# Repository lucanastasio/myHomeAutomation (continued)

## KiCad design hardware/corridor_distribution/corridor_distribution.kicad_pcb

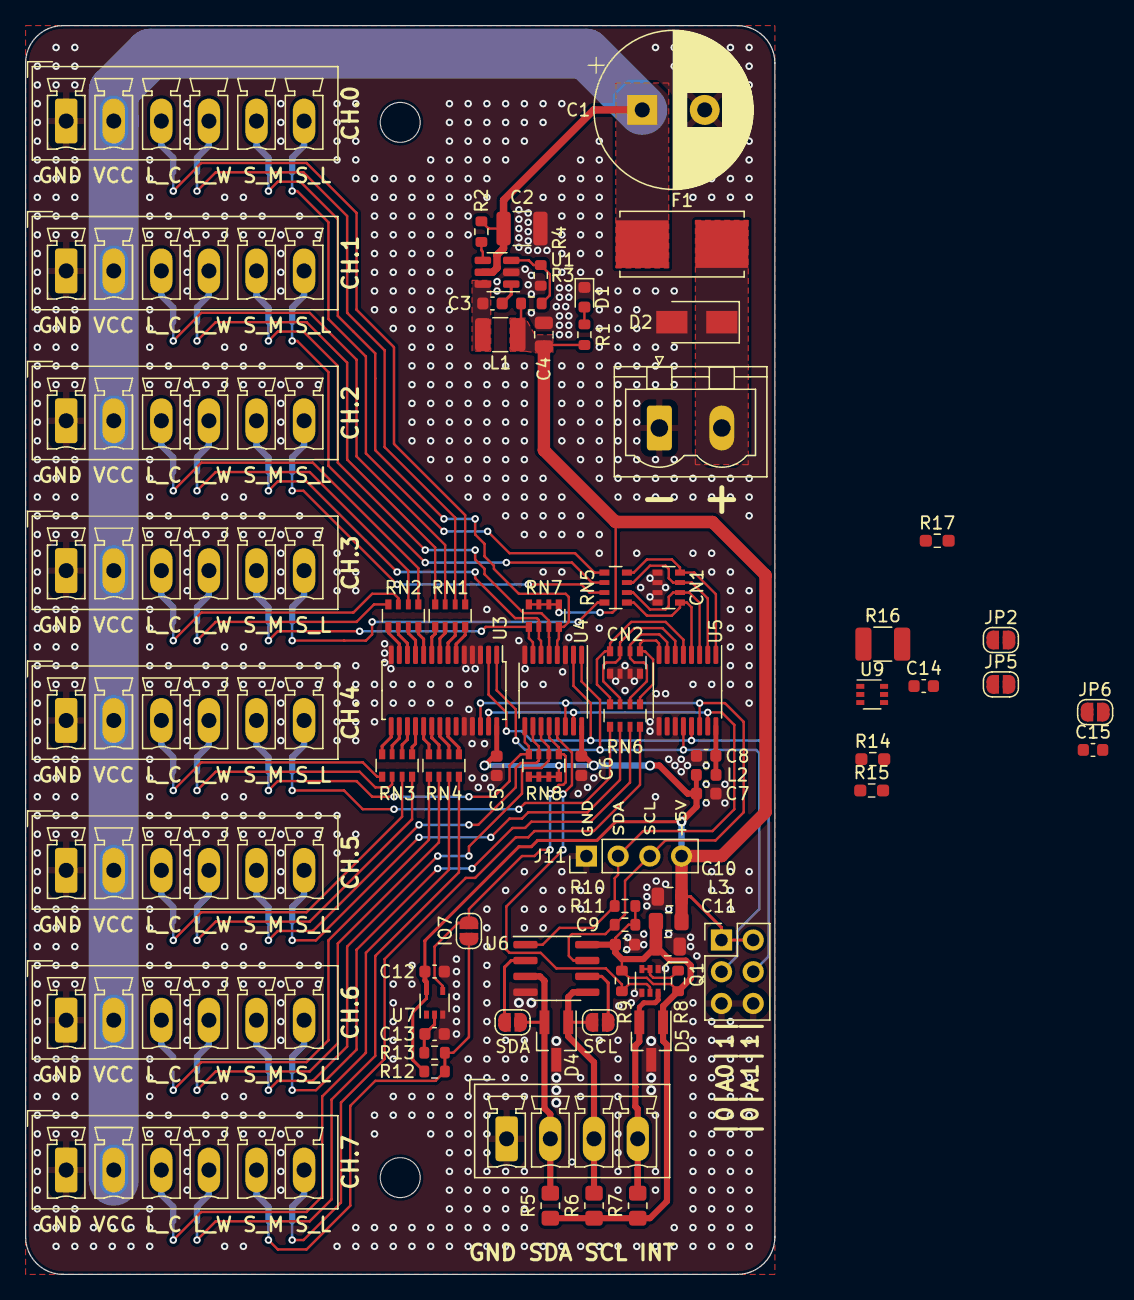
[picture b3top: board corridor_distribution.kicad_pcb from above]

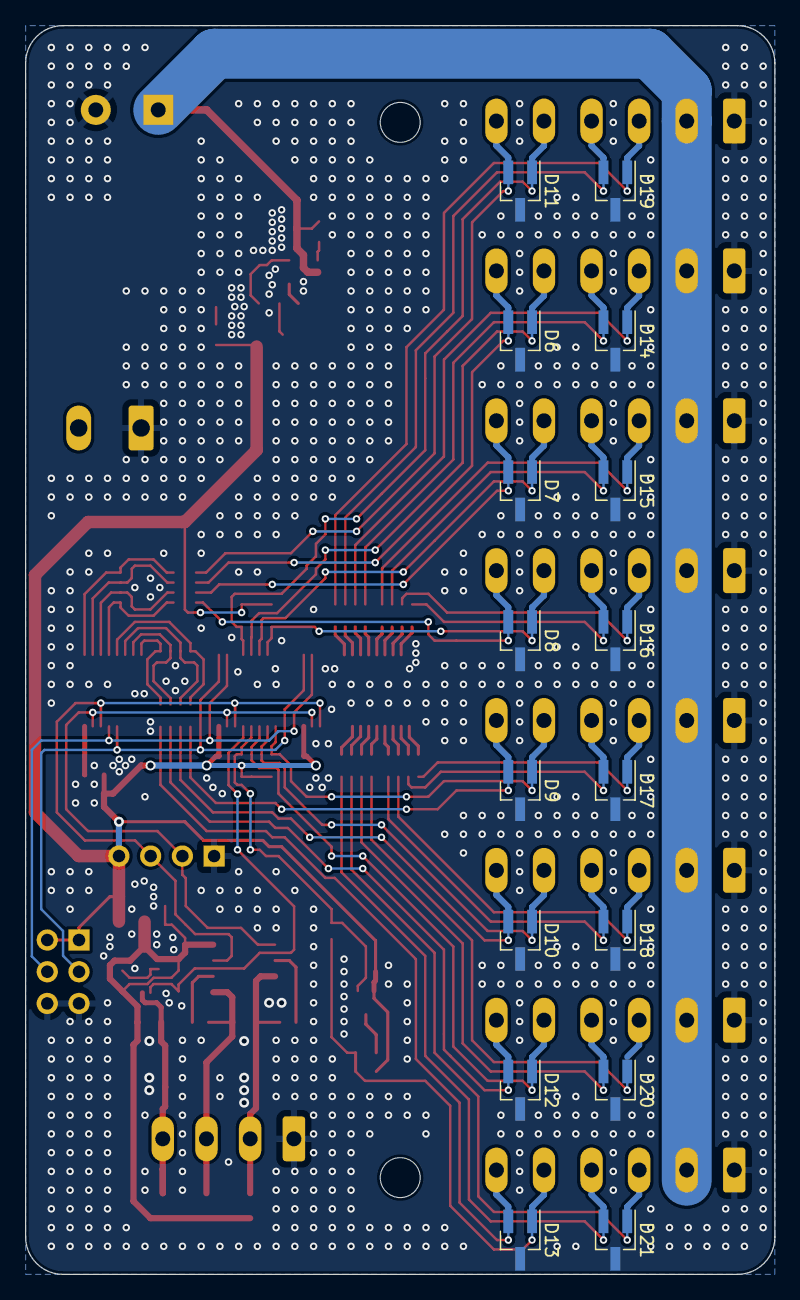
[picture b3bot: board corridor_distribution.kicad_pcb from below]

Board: 2 copper layers, 60.0 x 100.0 mm, 94 parts (16 on the bottom side), 86 nets.

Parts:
C1: 1000uF 50V D12.5xL25mm; CP_Radial_D12.5mm_P5.00mm
C2: 10u 50V; C_1210_3225Metric
C3, C5, C6, C7, C8, C9, C12, C13, C14, C15: 100n 50V; C_0603_1608Metric
C4, C10, C11: 22u 10V; C_0805_2012Metric
CN1, CN2: 100n 50V; R_Array_Convex_4x0603
D1: green LED; LED_0603_1608Metric
D2: SMAJ36A; D_SMA
D4, D5, D6, D7, D8, D9, D10, D11, D12, D13, D14, D15, D16, D17, D18, D19, D20, D21: SM05; SOT-23_Handsoldering
F1: 01550900M; Fuseholder_Littelfuse_Nano2_154x
H1, H2: MountingHole; MountingHole_3.2mm_M3
J1, J2, J3, J4, J5, J6, J7, J8: Screw_Terminal_01x06; PhoenixContact_MCV_1,5_6-G-3.81_1x06_P3.81mm_Vertical
J9: Screw_Terminal_01x02; PhoenixContact_MSTBVA_2,5_2-G_1x02_P5.00mm_Vertical
J10: Screw_Terminal_01x04; PhoenixContact_MCV_1,5_4-G-3.5_1x04_P3.50mm_Vertical
J11: Conn_01x04; PinHeader_1x04_P2.54mm_Vertical
J12: Conn_02x03_Odd_Even; PinHeader_2x03_P2.54mm_Vertical
JP1: IO7; SolderJumper-2_P1.3mm_Open_RoundedPad1.0x1.5mm
JP2, JP5, JP6: SolderJumper_2_Open; SolderJumper-2_P1.3mm_Open_RoundedPad1.0x1.5mm
JP3: SCL; SolderJumper-2_P1.3mm_Open_RoundedPad1.0x1.5mm
JP4: SDA; SolderJumper-2_P1.3mm_Open_RoundedPad1.0x1.5mm
L1: CBC3225T220KR; L_1210_3225Metric
L2: BLM18BD252SN1D; L_0603_1608Metric
L3: MMZ2012R102AT000; L_0805_2012Metric_Pad1.15x1.40mm_HandSolder
Q1: DMN2004DWK; SOT-363_SC-70-6
R1: 2.2k; R_0603_1608Metric
R2: 1M; R_0603_1608Metric
R3: 105k 0.5%; R_0603_1608Metric
R4: 20k 0.5%; R_0603_1608Metric
R5, R6, R7: 200; R_0805_2012Metric_Pad1.20x1.40mm_HandSolder
R8: 47k; R_0603_1608Metric
R9: 10k; R_0603_1608Metric
R10, R11, R12: 4.7k; R_0603_1608Metric
R13: 100k; R_0603_1608Metric
R14, R15: 330; R_0603_1608Metric_Pad0.98x0.95mm_HandSolder
R16: R; R_1210_3225Metric_Pad1.30x2.65mm_HandSolder
R17: R; R_0603_1608Metric_Pad0.98x0.95mm_HandSolder
RN1, RN2, RN3, RN4: 100; R_Array_Convex_4x0603
RN5, RN6: 68k; R_Array_Convex_4x0603
RN7, RN8: 4.7k; R_Array_Convex_4x0603
U1: TD1469; SOT-23-6
U3: PCA9685PW; TSSOP-28_4.4x9.7mm_P0.65mm
U4: TCA9554APW; TSSOP-16_4.4x5mm_P0.65mm
U5: ADS7830; TSSOP-16_4.4x5mm_P0.65mm
U6: P82B96; SOIC-8_3.9x4.9mm_P1.27mm
U7: 74LVC1G17; SOT-353_SC-70-5
U9: INA190; SOT-363_SC-70-6

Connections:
+5V: C4.2, C5.1, C6.1, C7.1, C10.1, C12.1, C14.1, J11.4, J12.1, J12.2, L1.2, L2.1, L3.1, R1.1, R3.1, R12.2, RN7.1 (R1.1), RN7.2 (R2.1), RN7.3 (R3.1), RN7.4 (R4.1), RN8.1 (R1.1), RN8.2 (R2.1), RN8.3 (R3.1), RN8.4 (R4.1), U3.28 (VDD), U4.16 (VDD), U7.5 (VCC), U9.3 (V+)
+5VA: C8.1, JP6.1 (A), L2.2, U5.16 (VDD)
+5VD: C9.1, C11.1, D5.1 (A1), L3.2, R5.1, R6.1, R7.1, R8.1, R9.1, R10.1, R11.1, U6.8 (VCC)
+36V: C1.1, C2.2, J1.2, J2.2, J3.2, J4.2, J5.2, J6.2, J7.2, J8.2, R2.2, R16.2, U1.5 (VIN), U9.5 (-)
/A0: J12.3, U3.1 (A0), U4.1 (A0), U5.12 (A0)
/A1: J12.4, U3.2 (A1), U4.2 (A1), U5.13 (A1)
/ADC/AD0: D11.2 (A2), J6.6, RN5.5 (R4.2)
/ADC/AD1: D6.2 (A2), J1.6, RN5.6 (R3.2)
/ADC/AD2: D7.2 (A2), J2.6, RN5.7 (R2.2)
/ADC/AD3: D8.2 (A2), J3.6, RN5.8 (R1.2)
/ADC/AD4: D9.2 (A2), J4.6, RN6.5 (R4.2)
/ADC/AD5: D10.2 (A2), J5.6, RN6.6 (R3.2)
/ADC/AD6: D12.2 (A2), J7.6, RN6.7 (R2.2)
/ADC/AD7: D13.2 (A2), J8.6, RN6.8 (R1.2)
/ADC/REF: C15.1, JP6.2 (B), U5.10 (REFin/REFout)
/ADC/_AD0: CN1.4 (R4.1), RN5.4 (R4.1), U5.1 (CH0)
/ADC/_AD1: CN1.3 (R3.1), RN5.3 (R3.1), U5.2 (CH1)
/ADC/_AD2: CN1.2 (R2.1), RN5.2 (R2.1), U5.3 (CH2)
/ADC/_AD3: CN1.1 (R1.1), RN5.1 (R1.1), U5.4 (CH3)
/ADC/_AD4: CN2.4 (R4.1), RN6.4 (R4.1), U5.5 (CH4)
/ADC/_AD5: CN2.3 (R3.1), RN6.3 (R3.1), U5.6 (CH5)
/ADC/_AD6: CN2.2 (R2.1), RN6.2 (R2.1), U5.7 (CH6)
/ADC/_AD7: CN2.1 (R1.1), R17.2, RN6.1 (R1.1), U5.8 (CH7)
/IO/IO0: D11.1 (A1), J6.5, RN7.8 (R1.2), U4.4 (P0)
/IO/IO1: D6.1 (A1), J1.5, RN7.7 (R2.2), U4.5 (P1)
/IO/IO2: D7.1 (A1), J2.5, RN7.6 (R3.2), U4.6 (P2)
/IO/IO3: D8.1 (A1), J3.5, RN7.5 (R4.2), U4.7 (P3)
/IO/IO4: D9.1 (A1), J4.5, RN8.8 (R1.2), U4.9 (P4)
/IO/IO5: D10.1 (A1), J5.5, RN8.7 (R2.2), U4.10 (P5)
/IO/IO6: D12.1 (A1), J7.5, RN8.6 (R3.2), U4.11 (P6)
/IO/IO7: D13.1 (A1), J8.5, JP1.2 (B), R12.1, R13.1
/IO/IO7F: C13.1, R13.2, U7.2
/IO/IO7S: JP1.1 (A), RN8.5 (R4.2), U4.12 (P7), U7.4
/SCL: J11.3, R11.2, U3.26 (SCL), U4.14 (SCL), U5.14 (SCL), U6.7 (SCL)
/SDA: J11.2, R10.2, U3.27 (SDA), U4.15 (SDA), U5.15 (SDA), U6.1 (SDA)
/bus_in/INT: D5.2 (A2), J10.4, Q1.6 (D), R7.2
/bus_in/SCL_{R}: JP3.1 (A), U6.6 (RXD-SCL)
/bus_in/SCL_{T}: D4.1 (A1), J10.3, JP3.2 (B), R6.2, U6.5 (TXD-SCL)
/bus_in/SDA_{R}: JP4.1 (A), U6.2 (RXD-SDA)
/bus_in/SDA_{T}: D4.2 (A2), J10.2, JP4.2 (B), R5.2, U6.3 (TXD-SDA)
/nodes/PW0: D19.1 (A1), J6.3, RN1.5 (R4.2)
/nodes/PW1: D19.2 (A2), J6.4, RN1.6 (R3.2)
/nodes/PW2: D14.1 (A1), J1.3, RN1.7 (R2.2)
/nodes/PW3: D14.2 (A2), J1.4, RN1.8 (R1.2)
/nodes/PW4: D15.1 (A1), J2.3, RN2.5 (R4.2)
/nodes/PW5: D15.2 (A2), J2.4, RN2.6 (R3.2)
/nodes/PW6: D16.1 (A1), J3.3, RN2.7 (R2.2)
/nodes/PW7: D16.2 (A2), J3.4, RN2.8 (R1.2)
/nodes/PW8: D17.1 (A1), J4.3, RN3.5 (R4.2)
/nodes/PW9: D17.2 (A2), J4.4, RN3.6 (R3.2)
/nodes/PW10: D18.1 (A1), J5.3, RN3.7 (R2.2)
/nodes/PW11: D18.2 (A2), J5.4, RN3.8 (R1.2)
/nodes/PW12: D20.1 (A1), J7.3, RN4.5 (R4.2)
/nodes/PW13: D20.2 (A2), J7.4, RN4.6 (R3.2)
/nodes/PW14: R15.1, RN4.7 (R2.2)
/nodes/PW15: R14.1, RN4.8 (R1.2)
/nodes/node conn 7/LED_C: D21.1 (A1), J8.3, R15.2
/nodes/node conn 7/LED_W: D21.2 (A2), J8.4, R14.2
/power_in/BST: C3.1, U1.1 (BOOST)
/power_in/EN: R2.1, U1.4 (EN)
/power_in/FB: R3.2, R4.1, U1.3 (VFB)
/power_in/SW: C3.2, L1.1, U1.6 (SW)
/pwm/_PW0: RN1.4 (R4.1), U3.6 (LED0)
/pwm/_PW1: RN1.3 (R3.1), U3.7 (LED1)
/pwm/_PW2: RN1.2 (R2.1), U3.8 (LED2)
/pwm/_PW3: RN1.1 (R1.1), U3.9 (LED3)
/pwm/_PW4: RN2.4 (R4.1), U3.10 (LED4)
/pwm/_PW5: RN2.3 (R3.1), U3.11 (LED5)
/pwm/_PW6: RN2.2 (R2.1), U3.12 (LED6)
/pwm/_PW7: RN2.1 (R1.1), U3.13 (LED7)
/pwm/_PW8: RN3.4 (R4.1), U3.15 (LED8)
/pwm/_PW9: RN3.3 (R3.1), U3.16 (LED9)
/pwm/_PW10: RN3.2 (R2.1), U3.17 (LED10)
/pwm/_PW11: RN3.1 (R1.1), U3.18 (LED11)
/pwm/_PW12: RN4.4 (R4.1), U3.19 (LED12)
/pwm/_PW13: RN4.3 (R3.1), U3.20 (LED13)
/pwm/_PW14: RN4.2 (R2.1), U3.21 (LED14)
/pwm/_PW15: RN4.1 (R1.1), U3.22 (LED15)
/pwm/~OE: JP5.1 (A), U3.23 (~OE)
/~INT: Q1.5 (G), R9.2, U4.13 (~INT)
GND: C1.2, C2.1, C4.1, C5.2, C6.2, C7.2, C8.2, C9.2, C10.2, C11.2, C12.2, C13.2, C14.2, C15.2, CN1.5 (R4.2), CN1.6 (R3.2), CN1.7 (R2.2), CN1.8 (R1.2), CN2.5 (R4.2), CN2.6 (R3.2), CN2.7 (R2.2), CN2.8 (R1.2), D1.1 (K), D2.2 (A), D4.3 (common), D5.3 (common), D6.3 (common), D7.3 (common), D8.3 (common), D9.3 (common), D10.3 (common), D11.3 (common), D12.3 (common), D13.3 (common), D14.3 (common), D15.3 (common), D16.3 (common), D17.3 (common), D18.3 (common), D19.3 (common), D20.3 (common), D21.3 (common), J1.1, J2.1, J3.1, J4.1, J5.1, J6.1, J7.1, J8.1, J9.1, J10.1, J11.1, J12.5, J12.6, JP2.1 (A), JP5.2 (B), Q1.1 (S), Q1.4 (S), R4.2, U1.2 (GND), U3.3 (A2), U3.4 (A3), U3.5 (A4), U3.14 (VSS), U3.24 (A5), U4.3 (A2), U4.8 (GND), U5.9 (GND), U5.11 (COM), U6.4 (GND), U7.3 (GND), U9.1 (REF), U9.2 (GND)
unnamed: D1.2 (A), R1.2
unnamed: JP2.2 (B), U3.25 (EXTCLK)
unnamed: Q1.2 (G), Q1.3 (D), R8.2
unnamed: F1.1, R16.1, U9.4 (+)
VBUS: D2.1 (K), F1.2, J9.2

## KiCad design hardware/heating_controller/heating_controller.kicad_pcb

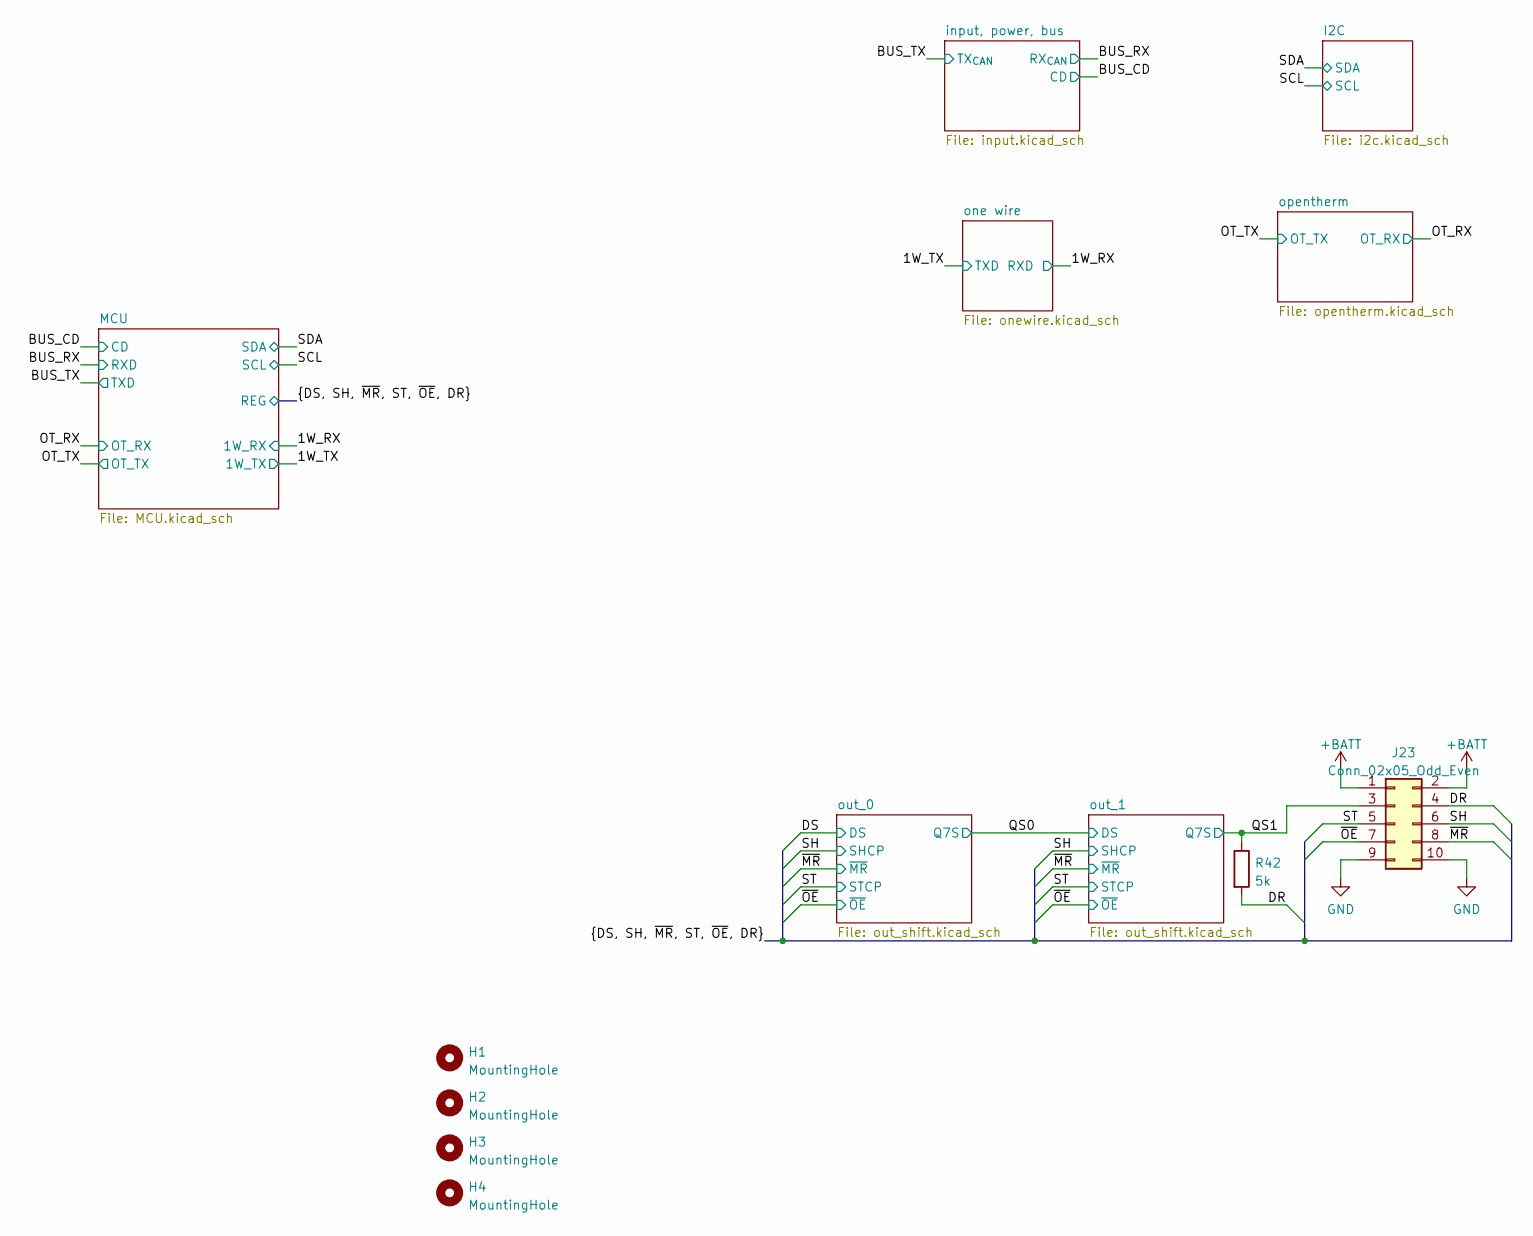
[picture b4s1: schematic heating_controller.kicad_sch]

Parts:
H1, H2, H3, H4: MountingHole; MountingHole_3.2mm_M3
J23: Conn_02x05_Odd_Even; IDC-Header_2x05_P2.54mm_Vertical
R42: 5k; R_0603_1608Metric

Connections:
+BATT: J23.1, J23.2; also elsewhere on the board
/DR: J23.4, R42.2; also elsewhere on the board
/QS1: J23.3, R42.1; also elsewhere on the board
/SH: J23.6; also elsewhere on the board
/ST: J23.5; also elsewhere on the board
/~MR: J23.8; also elsewhere on the board
/~OE: J23.7; also elsewhere on the board
GND: J23.9, J23.10; also elsewhere on the board

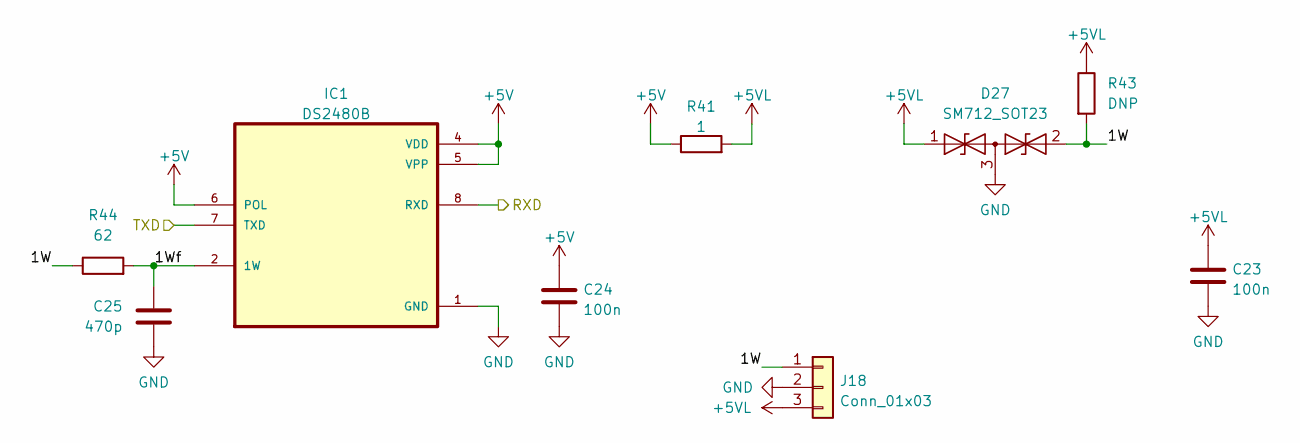
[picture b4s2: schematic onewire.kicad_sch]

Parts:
C23, C24: 100n; C_0603_1608Metric
C25: 470p; C_0603_1608Metric
D27: SM712_SOT23; SOT-23
IC1: DS2480B; SO-8_3.9x4.9mm_P1.27mm
J18: Conn_01x03; JST_PH_B3B-PH-K_1x03_P2.00mm_Vertical
R41: 1; R_0603_1608Metric
R43: DNP; R_0603_1608Metric
R44: 62; R_0603_1608Metric

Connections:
+5V: C24.2, IC1.4 (VDD), IC1.5 (VPP), IC1.6 (POL), R41.1; also elsewhere on the board
+5VL: C23.2, D27.1 (A1), J18.3, R41.2, R43.1
/1W_RX: IC1.8 (RXD); also elsewhere on the board
/1W_TX: IC1.7 (TXD); also elsewhere on the board
/one wire/1W: D27.2 (A2), J18.1, R43.2, R44.1
/one wire/1Wf: C25.1, IC1.2 (1W), R44.2
GND: C23.1, C24.1, C25.2, D27.3 (common), IC1.1 (GND), J18.2; also elsewhere on the board

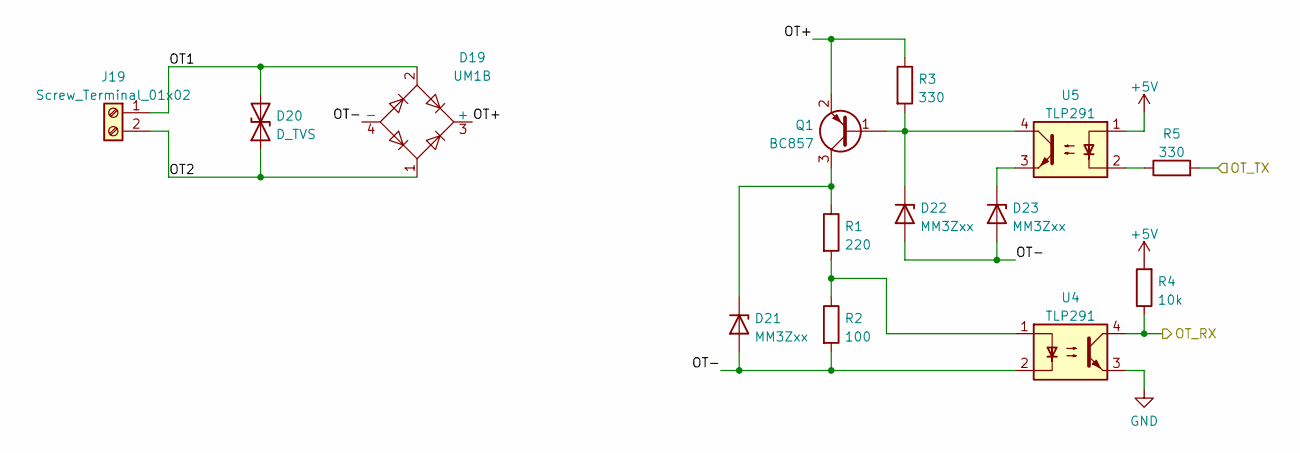
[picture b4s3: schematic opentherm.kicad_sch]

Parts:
D19: UM1B; UMB
D20: D_TVS; Nexperia_CFP3_SOD-123W
D21, D22, D23: MM3Zxx; D_SOD-323_HandSoldering
J19: Screw_Terminal_01x02; PhoenixContact_MCV_1,5_2-G-3.81_1x02_P3.81mm_Vertical
Q1: BC857; SOT-23
R1: 220; R_0603_1608Metric
R2: 100; R_0603_1608Metric
R3, R5: 330; R_0603_1608Metric
R4: 10k; R_0603_1608Metric
U4, U5: TLP291; SOIC-4_4.55x2.6mm_P1.27mm

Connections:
+5V: R4.2, U5.1; also elsewhere on the board
/OT_RX: R4.1, U4.4; also elsewhere on the board
/OT_TX: R5.2; also elsewhere on the board
/opentherm/OT1: D19.2, D20.2 (A2), J19.1
/opentherm/OT2: D19.1, D20.1 (A1), J19.2
/opentherm/OT+: D19.3 (+), Q1.2 (E), R3.1
/opentherm/OT-: D19.4 (-), D21.2 (A), D22.2 (A), D23.2 (A), R2.2, U4.2
GND: U4.3; also elsewhere on the board
unnamed: D21.1 (K), Q1.3 (C), R1.1
unnamed: D22.1 (K), Q1.1 (B), R3.2, U5.4
unnamed: D23.1 (K), U5.3
unnamed: R1.2, R2.1, U4.1
unnamed: R5.1, U5.2

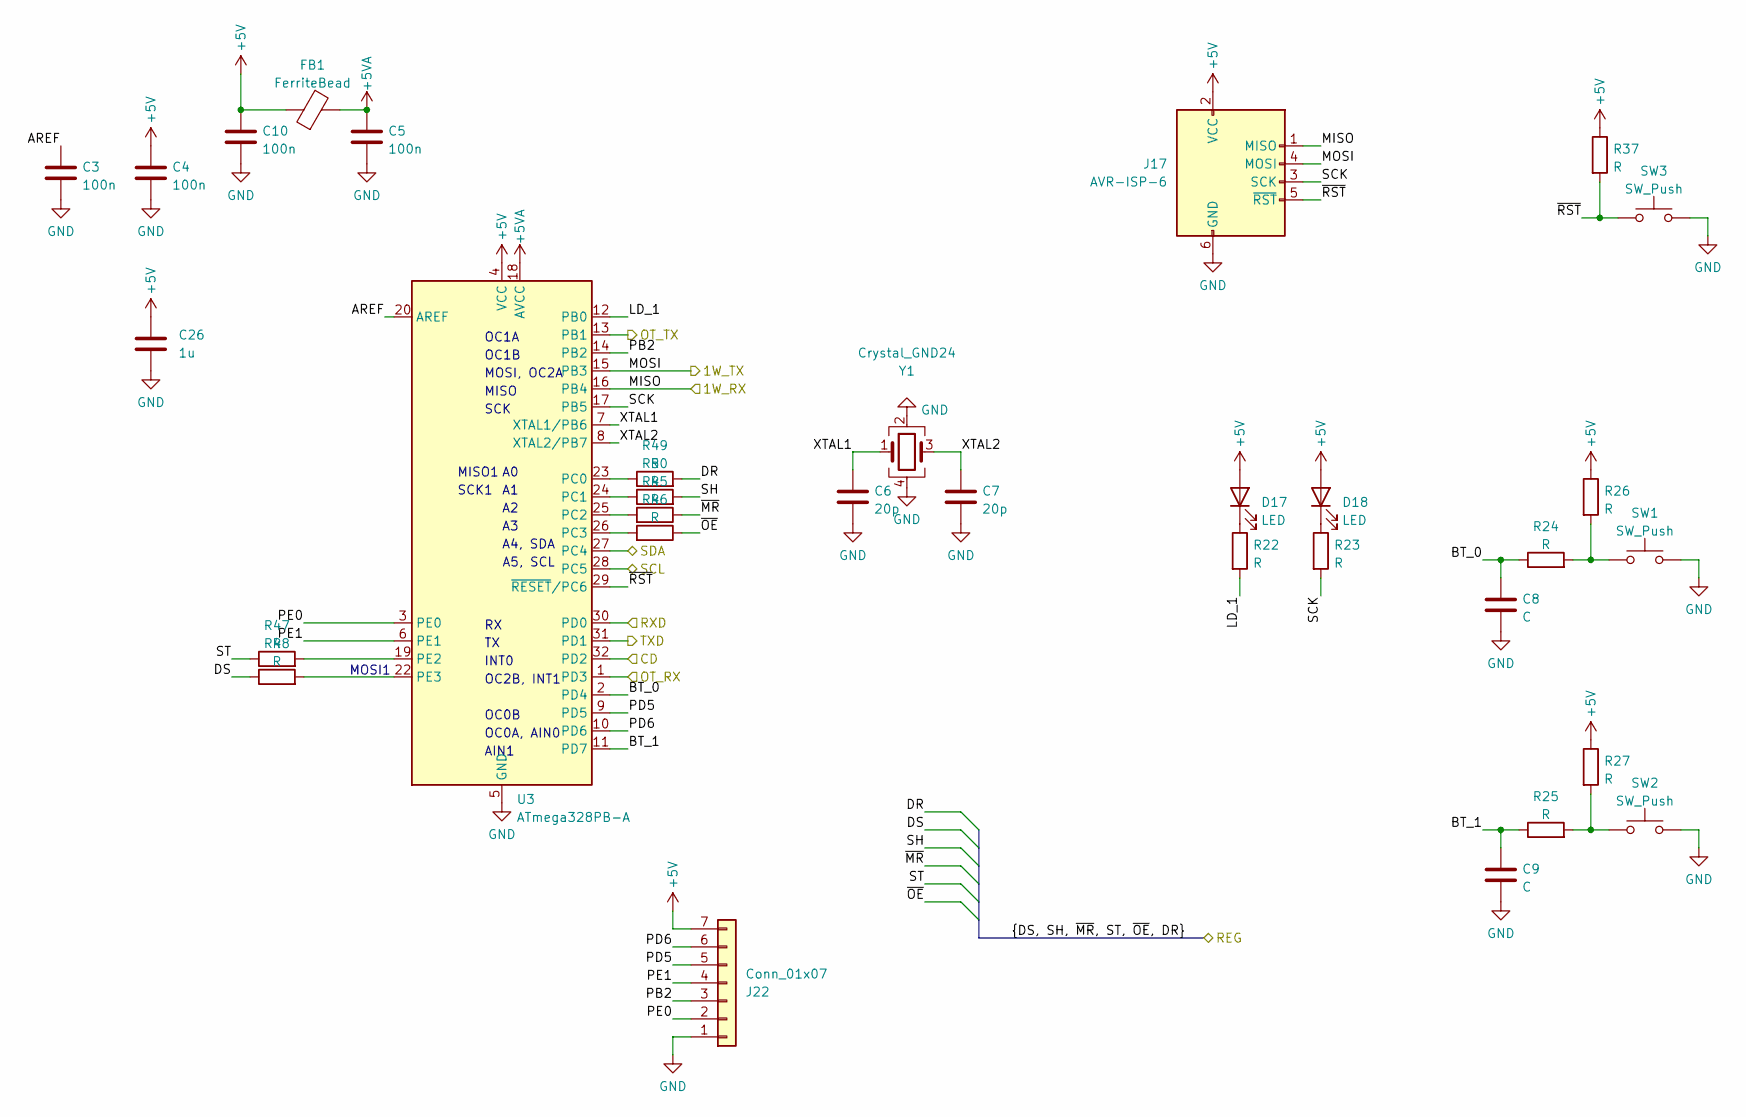
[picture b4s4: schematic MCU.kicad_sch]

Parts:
C3, C4, C5, C10: 100n; C_0603_1608Metric
C6, C7: 20p; C_0603_1608Metric
C8, C9: C; C_0603_1608Metric
C26: 1u; C_0603_1608Metric
D17, D18: LED; LED_0603_1608Metric
FB1: FerriteBead; L_0603_1608Metric
J17: AVR-ISP-6; PinHeader_2x03_P2.54mm_Vertical
J22: Conn_01x07; PinHeader_1x07_P2.54mm_Vertical
R22, R23, R24, R25, R26, R27, R37, R45, R46, R47, R48, R49, R50: R; R_0603_1608Metric
SW1, SW2, SW3: SW_Push; SW_SPST_B3U-1000P
U3: ATmega328PB-A; TQFP-32_7x7mm_P0.8mm
Y1: Crystal_GND24; Crystal_SMD_3225-4Pin_3.2x2.5mm

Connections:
+5V: C4.2, C10.1, C26.2, D17.2 (A), D18.2 (A), FB1.1, J17.2 (VCC), J22.7, R26.1, R27.1, R37.1, U3.4 (VCC); also elsewhere on the board
+5VA: C5.1, FB1.2, U3.18 (AVCC)
/1W_RX: J17.1 (MISO), U3.16 (PB4); also elsewhere on the board
/1W_TX: J17.4 (MOSI), U3.15 (PB3); also elsewhere on the board
/BUS_CD: U3.32 (PD2); also elsewhere on the board
/BUS_RX: U3.30 (PD0); also elsewhere on the board
/BUS_TX: U3.31 (PD1); also elsewhere on the board
/DR: R49.2; also elsewhere on the board
/DS: R48.1; also elsewhere on the board
/MCU/AREF: C3.1, U3.20 (AREF)
/MCU/BT_0: C8.1, R24.1, U3.2 (PD4)
/MCU/BT_1: C9.1, R25.1, U3.11 (PD7)
/MCU/LD_1: R22.2, U3.12 (PB0)
/MCU/PB2: J22.3, U3.14 (PB2)
/MCU/PD5: J22.5, U3.9 (PD5)
/MCU/PD6: J22.6, U3.10 (PD6)
/MCU/PE0: J22.2, U3.3 (PE0)
/MCU/PE1: J22.4, U3.6 (PE1)
/MCU/SCK: J17.3 (SCK), R23.2, U3.17 (PB5)
/MCU/XTAL1: C6.1, U3.7 (XTAL1/PB6), Y1.1
/MCU/XTAL2: C7.1, U3.8 (XTAL2/PB7), Y1.3
/MCU/~RST: J17.5 (~RST), R37.2, SW3.1, U3.29 (~RESET/PC6)
/OT_RX: U3.1 (PD3); also elsewhere on the board
/OT_TX: U3.13 (PB1); also elsewhere on the board
/SCL: U3.28 (PC5); also elsewhere on the board
/SDA: U3.27 (PC4); also elsewhere on the board
/SH: R50.2; also elsewhere on the board
/ST: R47.1; also elsewhere on the board
/~MR: R45.1; also elsewhere on the board
/~OE: R46.1; also elsewhere on the board
GND: C3.2, C4.1, C5.2, C6.2, C7.2, C8.2, C9.2, C10.2, C26.1, J17.6 (GND), J22.1, SW1.2, SW2.2, SW3.2, U3.5 (GND), U3.21 (GND), Y1.2, Y1.4; also elsewhere on the board
unnamed: D17.1 (K), R22.1
unnamed: D18.1 (K), R23.1
unnamed: R24.2, R26.2, SW1.1
unnamed: R25.2, R27.2, SW2.1
unnamed: R49.1, U3.23 (PC0)
unnamed: R50.1, U3.24 (PC1)
unnamed: R45.2, U3.25 (PC2)
unnamed: R46.2, U3.26 (PC3)
unnamed: R47.2, U3.19 (PE2)
unnamed: R48.2, U3.22 (PE3)

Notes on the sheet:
OC0B
OC1B
OC1A
MISO
SCK1
A4, SDA
OC2B, INT1
INT0
OC0A, AIN0
MOSI, OC2A
SCK
MISO1
AIN1
A5, SCL
MOSI1

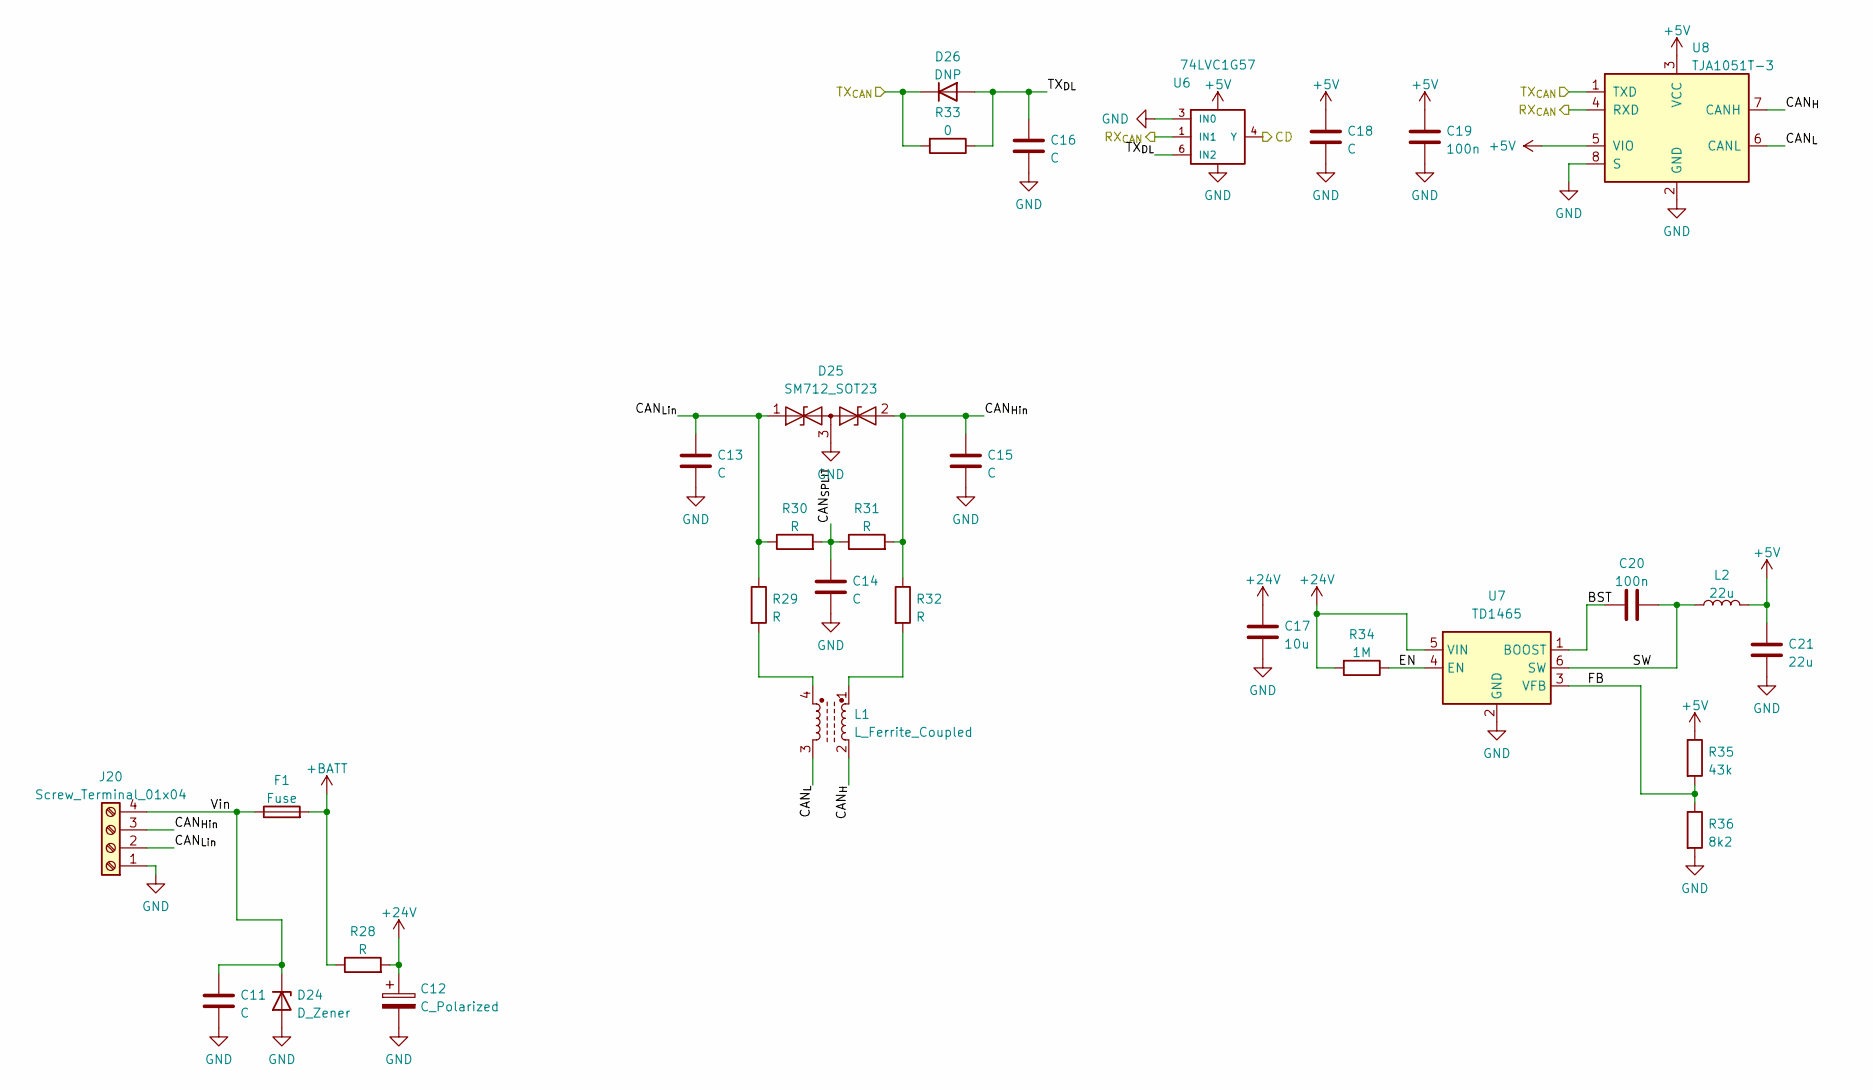
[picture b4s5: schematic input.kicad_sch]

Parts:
C11, C13, C15, C16, C18: C; C_0603_1608Metric
C12: C_Polarized; CP_Radial_D6.3mm_P2.50mm
C14: C; C_0805_2012Metric_Pad1.18x1.45mm_HandSolder
C17: 10u; C_1206_3216Metric
C19, C20: 100n; C_0603_1608Metric
C21: 22u; C_0805_2012Metric
D24: D_Zener; D_SMA
D25: SM712_SOT23; SOT-23
D26: DNP; D_SOD-523
F1: Fuse; Fuse_1206_3216Metric_Pad1.42x1.75mm_HandSolder
J20: Screw_Terminal_01x04; PhoenixContact_MCV_1,5_4-G-3.81_1x04_P3.81mm_Vertical
L1: L_Ferrite_Coupled; L_CommonModeChoke_Coilcraft_0805USB
L2: 22u; L_1210_3225Metric
R28: R; R_0805_2012Metric
R29, R32: R; R_0603_1608Metric
R30, R31: R; R_0805_2012Metric_Pad1.20x1.40mm_HandSolder
R33: 0; R_0603_1608Metric
R34: 1M; R_0603_1608Metric
R35: 43k; R_0603_1608Metric
R36: 8k2; R_0603_1608Metric
U6: 74LVC1G57; SOT-563
U7: TD1465; SOT-23-6
U8: TJA1051T-3; SOIC-8_3.9x4.9mm_P1.27mm

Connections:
+5V: C18.1, C19.2, C21.2, L2.2, R35.1, U6.5 (VCC), U8.3 (VCC), U8.5 (VIO); also elsewhere on the board
+24V: C12.1, C17.2, R28.2, R34.2, U7.5 (VIN)
+BATT: F1.2, R28.1; also elsewhere on the board
/BUS_CD: U6.4 (Y); also elsewhere on the board
/BUS_RX: U6.1 (IN1), U8.4 (RXD); also elsewhere on the board
/BUS_TX: D26.1 (K), R33.2, U8.1 (TXD); also elsewhere on the board
/input, power, bus/BST: C20.1, U7.1 (BOOST)
/input, power, bus/CAN_{Hin}: C15.1, D25.2 (A2), J20.3, R31.2, R32.1
/input, power, bus/CAN_{H}: L1.2, U8.7 (CANH)
/input, power, bus/CAN_{Lin}: C13.1, D25.1 (A1), J20.2, R29.1, R30.1
/input, power, bus/CAN_{L}: L1.3, U8.6 (CANL)
/input, power, bus/CAN_{SPLIT}: C14.1, R30.2, R31.1
/input, power, bus/EN: R34.1, U7.4 (EN)
/input, power, bus/FB: R35.2, R36.1, U7.3 (VFB)
/input, power, bus/SW: C20.2, L2.1, U7.6 (SW)
/input, power, bus/TX_{DL}: C16.1, D26.2 (A), R33.1, U6.6 (IN2)
/input, power, bus/Vin: C11.1, D24.1 (K), F1.1, J20.4
GND: C11.2, C12.2, C13.2, C14.2, C15.2, C16.2, C17.1, C18.2, C19.1, C21.1, D24.2 (A), D25.3 (common), J20.1, R36.2, U6.2 (GND), U6.3 (IN0), U7.2 (GND), U8.2 (GND), U8.8 (S); also elsewhere on the board
unnamed: L1.1, R32.2
unnamed: L1.4, R29.2

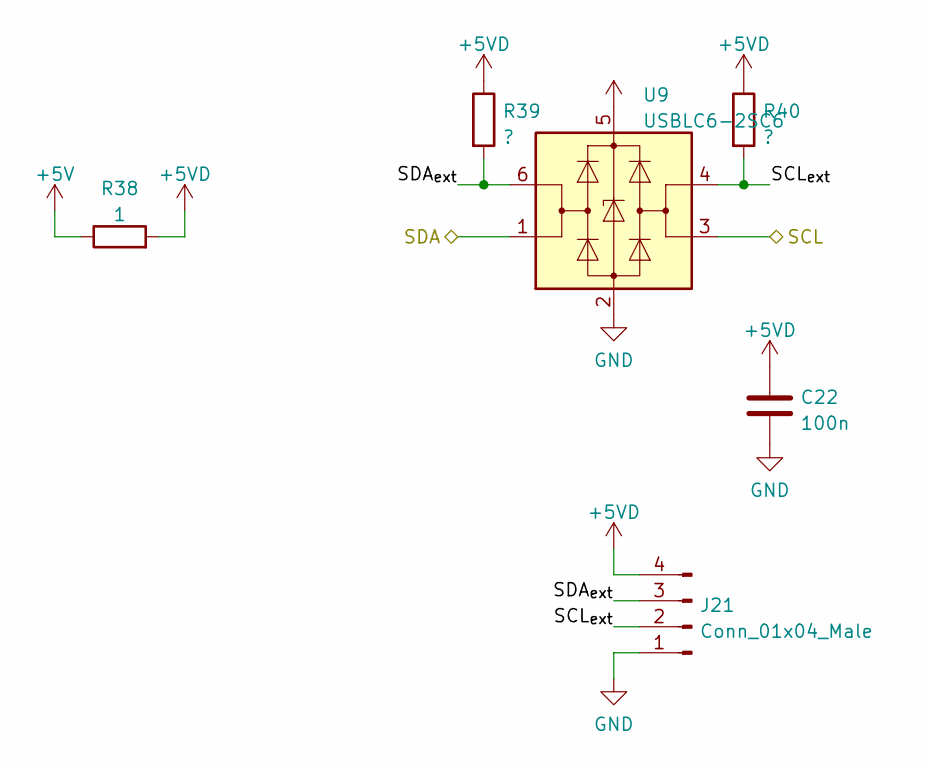
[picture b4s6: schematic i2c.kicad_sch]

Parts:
C22: 100n; C_0603_1608Metric
J21: Conn_01x04_Male; TerminalBlock_Phoenix_MPT-0,5-4-2.54_1x04_P2.54mm_Horizontal
R38: 1; R_0603_1608Metric
R39, R40: ?; R_0603_1608Metric
U9: USBLC6-2SC6; SOT-23-6

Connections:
+5V: R38.1; also elsewhere on the board
/I2C/SCL_{ext}: J21.2, R40.2, U9.4 (I/O2)
/I2C/SDA_{ext}: J21.3, R39.2, U9.6 (I/O1)
/SCL: U9.3 (I/O2); also elsewhere on the board
/SDA: U9.1 (I/O1); also elsewhere on the board
GND: C22.1, J21.1, U9.2 (GND); also elsewhere on the board

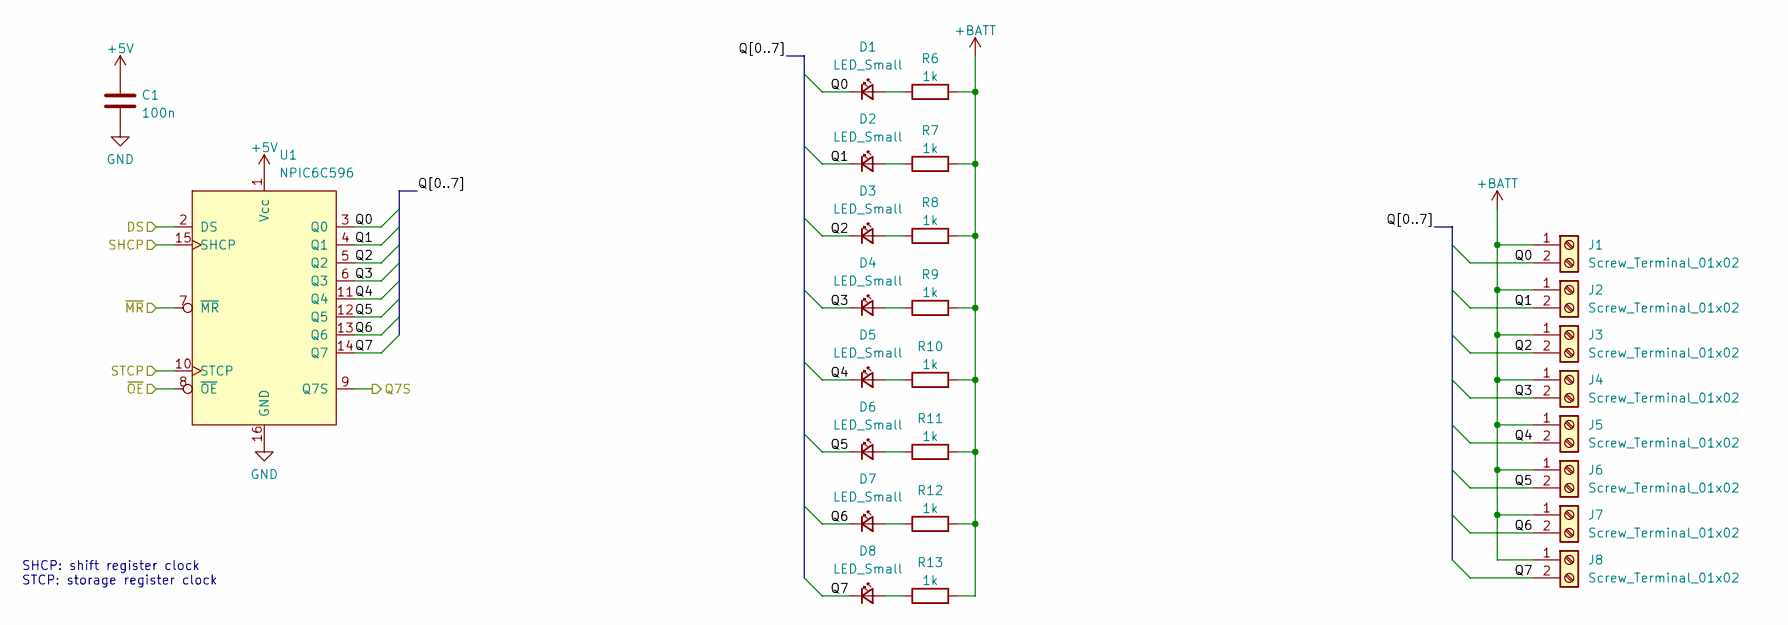
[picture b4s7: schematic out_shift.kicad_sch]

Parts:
C1: 100n; C_0603_1608Metric
D1, D2, D3, D4, D5, D6, D7, D8: LED_Small; LED_0603_1608Metric
J1, J2, J3, J4, J5, J6, J7, J8: Screw_Terminal_01x02; PhoenixContact_MCV_1,5_2-G-3.81_1x02_P3.81mm_Vertical
R6, R7, R8, R9, R10, R11, R12, R13: 1k; R_0603_1608Metric
U1: NPIC6C596; SO-16_3.9x9.9mm_P1.27mm

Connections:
+5V: C1.1, U1.1 (Vcc); also elsewhere on the board
+BATT: J1.1, J2.1, J3.1, J4.1, J5.1, J6.1, J7.1, J8.1, R6.2, R7.2, R8.2, R9.2, R10.2, R11.2, R12.2, R13.2; also elsewhere on the board
/DS: U1.2 (DS); also elsewhere on the board
/QS0: U1.9 (Q7S); also elsewhere on the board
/SH: U1.15 (SHCP); also elsewhere on the board
/ST: U1.10 (STCP); also elsewhere on the board
/out_0/Q0: D1.1 (K), J1.2, U1.3 (Q0)
/out_0/Q1: D2.1 (K), J2.2, U1.4 (Q1)
/out_0/Q2: D3.1 (K), J3.2, U1.5 (Q2)
/out_0/Q3: D4.1 (K), J4.2, U1.6 (Q3)
/out_0/Q4: D5.1 (K), J5.2, U1.11 (Q4)
/out_0/Q5: D6.1 (K), J6.2, U1.12 (Q5)
/out_0/Q6: D7.1 (K), J7.2, U1.13 (Q6)
/out_0/Q7: D8.1 (K), J8.2, U1.14 (Q7)
/~MR: U1.7 (~MR); also elsewhere on the board
/~OE: U1.8 (~OE); also elsewhere on the board
GND: C1.2, U1.16 (GND); also elsewhere on the board
unnamed: D1.2 (A), R6.1
unnamed: D2.2 (A), R7.1
unnamed: D3.2 (A), R8.1
unnamed: D4.2 (A), R9.1
unnamed: D5.2 (A), R10.1
unnamed: D6.2 (A), R11.1
unnamed: D7.2 (A), R12.1
unnamed: D8.2 (A), R13.1

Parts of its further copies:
C2: 100n; C_0603_1608Metric
D9, D10, D11, D12, D13, D14, D15, D16: LED_Small; LED_0603_1608Metric
J9, J10, J11, J12, J13, J14, J15, J16: Screw_Terminal_01x02; PhoenixContact_MCV_1,5_2-G-3.81_1x02_P3.81mm_Vertical
R14, R15, R16, R17, R18, R19, R20, R21: 1k; R_0603_1608Metric
U2: NPIC6C596; SO-16_3.9x9.9mm_P1.27mm

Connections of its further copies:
+5V: C2.1, U2.1 (Vcc); also elsewhere on the board
+BATT: J9.1, J10.1, J11.1, J12.1, J13.1, J14.1, J15.1, J16.1, R14.2, R15.2, R16.2, R17.2, R18.2, R19.2, R20.2, R21.2; also elsewhere on the board
/QS0: U2.2 (DS); also elsewhere on the board
/QS1: U2.9 (Q7S); also elsewhere on the board
/SH: U2.15 (SHCP); also elsewhere on the board
/ST: U2.10 (STCP); also elsewhere on the board
/out_1/Q0: D9.1 (K), J9.2, U2.3 (Q0)
/out_1/Q1: D10.1 (K), J10.2, U2.4 (Q1)
/out_1/Q2: D11.1 (K), J11.2, U2.5 (Q2)
/out_1/Q3: D12.1 (K), J12.2, U2.6 (Q3)
/out_1/Q4: D13.1 (K), J13.2, U2.11 (Q4)
/out_1/Q5: D14.1 (K), J14.2, U2.12 (Q5)
/out_1/Q6: D15.1 (K), J15.2, U2.13 (Q6)
/out_1/Q7: D16.1 (K), J16.2, U2.14 (Q7)
/~MR: U2.7 (~MR); also elsewhere on the board
/~OE: U2.8 (~OE); also elsewhere on the board
GND: C2.2, U2.16 (GND); also elsewhere on the board
unnamed: D9.2 (A), R14.1
unnamed: D10.2 (A), R15.1
unnamed: D11.2 (A), R16.1
unnamed: D12.2 (A), R17.1
unnamed: D13.2 (A), R18.1
unnamed: D14.2 (A), R19.1
unnamed: D15.2 (A), R20.1
unnamed: D16.2 (A), R21.1

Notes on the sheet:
SHCP: shift register clock STCP: storage register clock

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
